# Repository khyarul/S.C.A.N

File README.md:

# S.C.A.N
 Small and Cheap Attendance Node

## Attendance Node Machine
   - Hardware: ESP8266 Wemos D1 Mini - Software: Arduino C/C++

   - Feature and library used:
     - [x] Dual Mode: **Tap to Unlock Door** and **Attendance Mode**
     - [x] Scheduler.h (Multitask) from [Here](https://github.com/nrwiersma/ESP8266Scheduler)
     - [x] PubSubClient.h (MQTT protocol client)
     - [x] LiquidCrystal_I2C.h (LCD16x2 I2C)
     - [x] MFRC522.h (RFID SPI module 13.56MHz)
     - [x] ArduinoOTA.h (wireless/no-usb programming)
     - [x] Reed/magnetic sensor for Door state
     - [x] solenoid door lock port max. 12V/1A (12W)
     - [x] 5V/3A (15W) power supply input
   
   - Recommended ESP8266 Wemos D1 Mini Arduino Configuration:

   - Wemos D1 Mini Port Allocation:
   
 PORT |	FUNCTION |	DEVICE
 -----|----------|-------   
 D1 |	I2C SCL |	LCD 16x2
 D2 |	I2C SDA |	LCD 16x2
 D4 |	SPI Reset |	RC522
 D5 |	SPI SCK |	RC522
 D6 |	SPI MISO |	RC522
 D7 |	SPI MOSI	| RC522
 D8 |	SPI SS	| RC522
 D0 |	Digital Output	| Solenoid
 TX |	Digital Input	| Attendance Mode button
 RX |	Digital Output |	Buzzer
 D3 |	Digital Input |	“Unlock Door” Mode button
 A0 |	Analog Input |	Magnetic Switch/Sensor

   - Mechanic Documentation Photo:
     - **Acrylic Case for LCD, RFID sensor, button, and buzzer. Install it outside the room.**

     - **Acrylic case for controller part, reed/magnet sensor and solenoid port. Install it inside the room.**

     - **Solenoid port and small hole for reed/magnet sensor wire**

## GUI (Node Monitor & Employee Manager)
- Tested on Windows 10 PC and Ubuntu Mate 18.04 64bit on Raspberry Pi 3 (Should be supported with Ubuntu 64bit on PC)
- Main file: **"SCAN_node_monitor.py"** (**"karyawan.py"**, **"icons"**, and **"images" need to be in the same folder**)

- Feature:
  - [x] Manage & monitor all Node Machine that connected to the same MQTT server.
  - [x] Using MongoDB database for Node & Employee Manager.
  - [x] Unlock door on every Node Machine remotely.

- Python 3.7 module/library used:
  - [x] Pyqt5 (for GUI)
  - [x] PyMongo (for MongoDB Database driver)
  - [x] Paho-Mqtt (MQTT client)
  - [x] Threading (Multitasking using Multithreading, 1 thread per 1 Attendance Node Machine)

## Support & DONATE this open source project:
  - PAYPAL  : [SentinelCreative](https://www.paypal.me/sentinelcreative "PAYPAL")
  - BNI     : 1284959883 (Khyarul Arham)
  - Jago    : 504120557241 (Khyarul Arham)

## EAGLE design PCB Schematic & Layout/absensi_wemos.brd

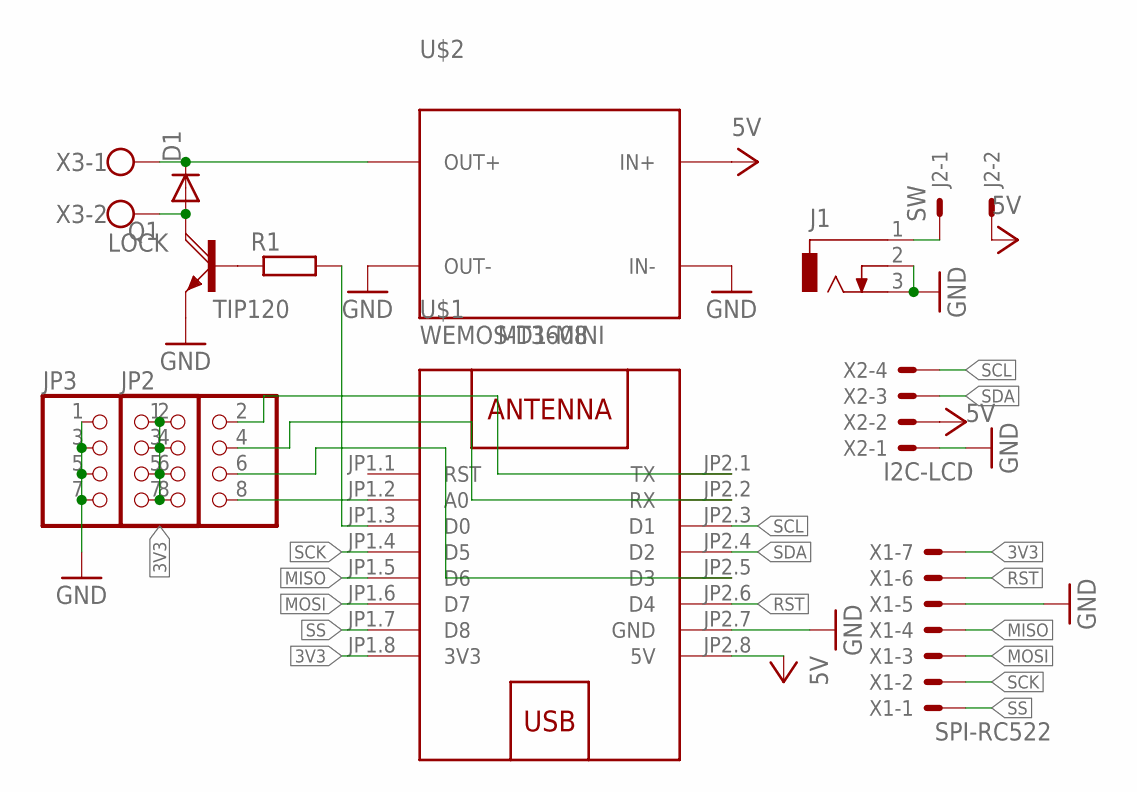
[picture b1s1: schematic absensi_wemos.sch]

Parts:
D1: DIODE-DO-214AC; DO-214AC
J1: DCJ0303
J2: SW; 6410-02
JP2, JP3: PINHD-2X4; 2X04
Q1: TIP120; TO220AH
R1: R0207/10; 0207/10
U$1: WEMOS-D1-MINI
U$2: MT3608; DC-DC-STEP-UP-MT3608
X1: SPI-RC522; 6410-07
X2: I2C-LCD; 6410-04
X3: LOCK; W237-102

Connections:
3V3: JP2.1, JP2.3, JP2.5, JP2.7, JP3.2, JP3.4, JP3.6, JP3.8, U$1.JP1.8 (3V3), X1.7
GND: J1.2, J1.3, JP3.1, JP3.3, JP3.5, JP3.7, Q1.E, U$1.JP2.7 (GND), U$2.IN-, U$2.OUT-, X1.5, X2.1
MISO: U$1.JP1.5 (D6), X1.4
MOSI: U$1.JP1.6 (D7), X1.3
unnamed: J1.1, J2.1
unnamed: R1.2, U$1.JP1.3 (D0)
unnamed: Q1.B, R1.1
unnamed: D1.C, U$2.OUT+, X3.1
unnamed: D1.A, Q1.C, X3.2
unnamed: JP2.8, U$1.JP1.2 (A0)
unnamed: JP2.6, U$1.JP2.5 (D3)
unnamed: JP2.4, U$1.JP2.2 (RX)
unnamed: JP2.2, U$1.JP2.1 (TX)
RST: U$1.JP2.6 (D4), X1.6
SCK: U$1.JP1.4 (D5), X1.2
SCL: U$1.JP2.3 (D1), X2.4
SDA: U$1.JP2.4 (D2), X2.3
SS: U$1.JP1.7 (D8), X1.1
VCC: J2.2, U$1.JP2.8 (5V), U$2.IN+, X2.2

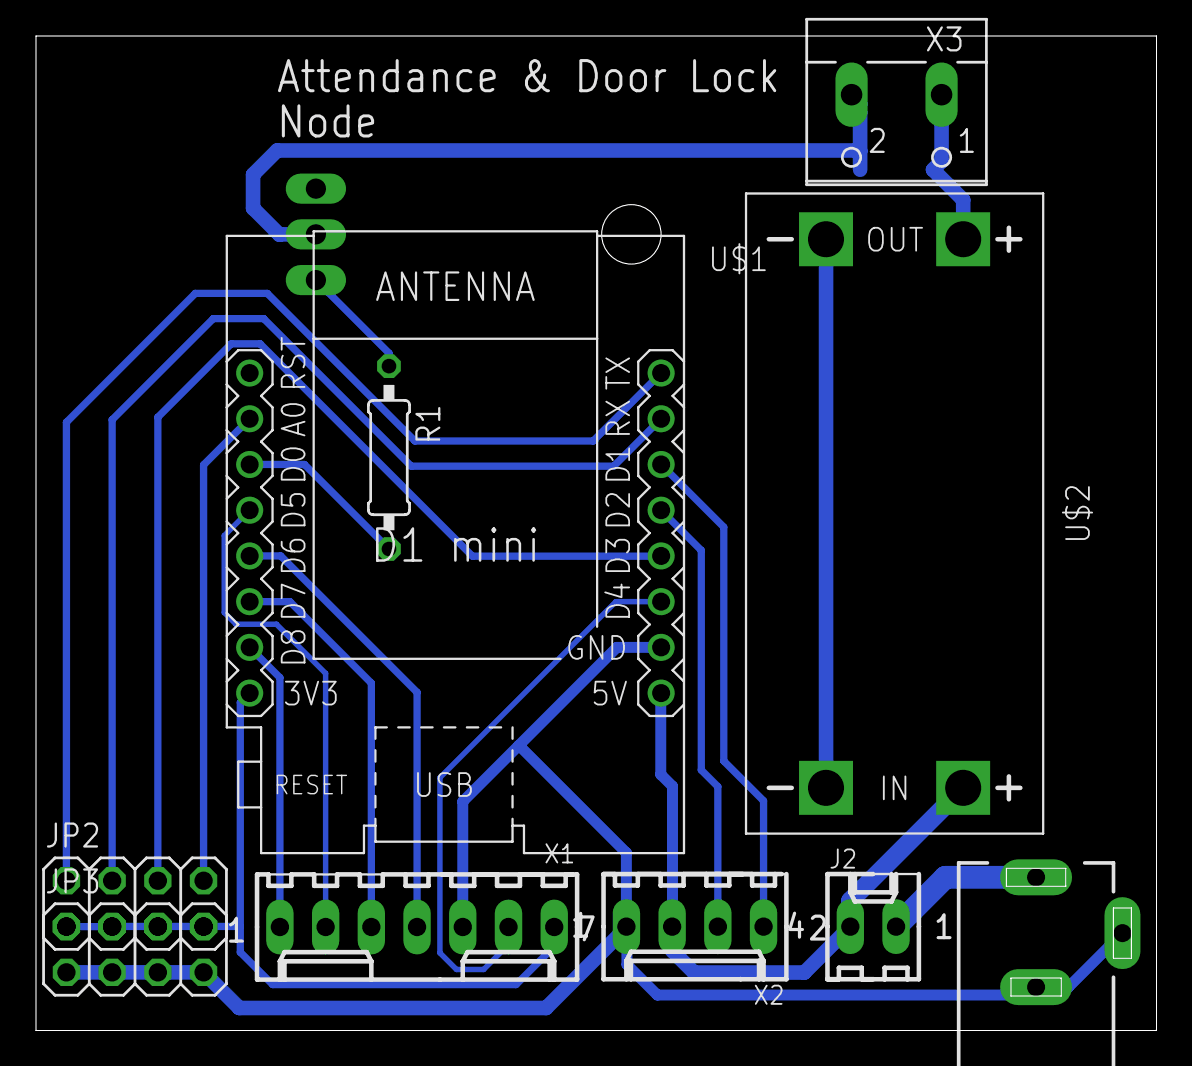
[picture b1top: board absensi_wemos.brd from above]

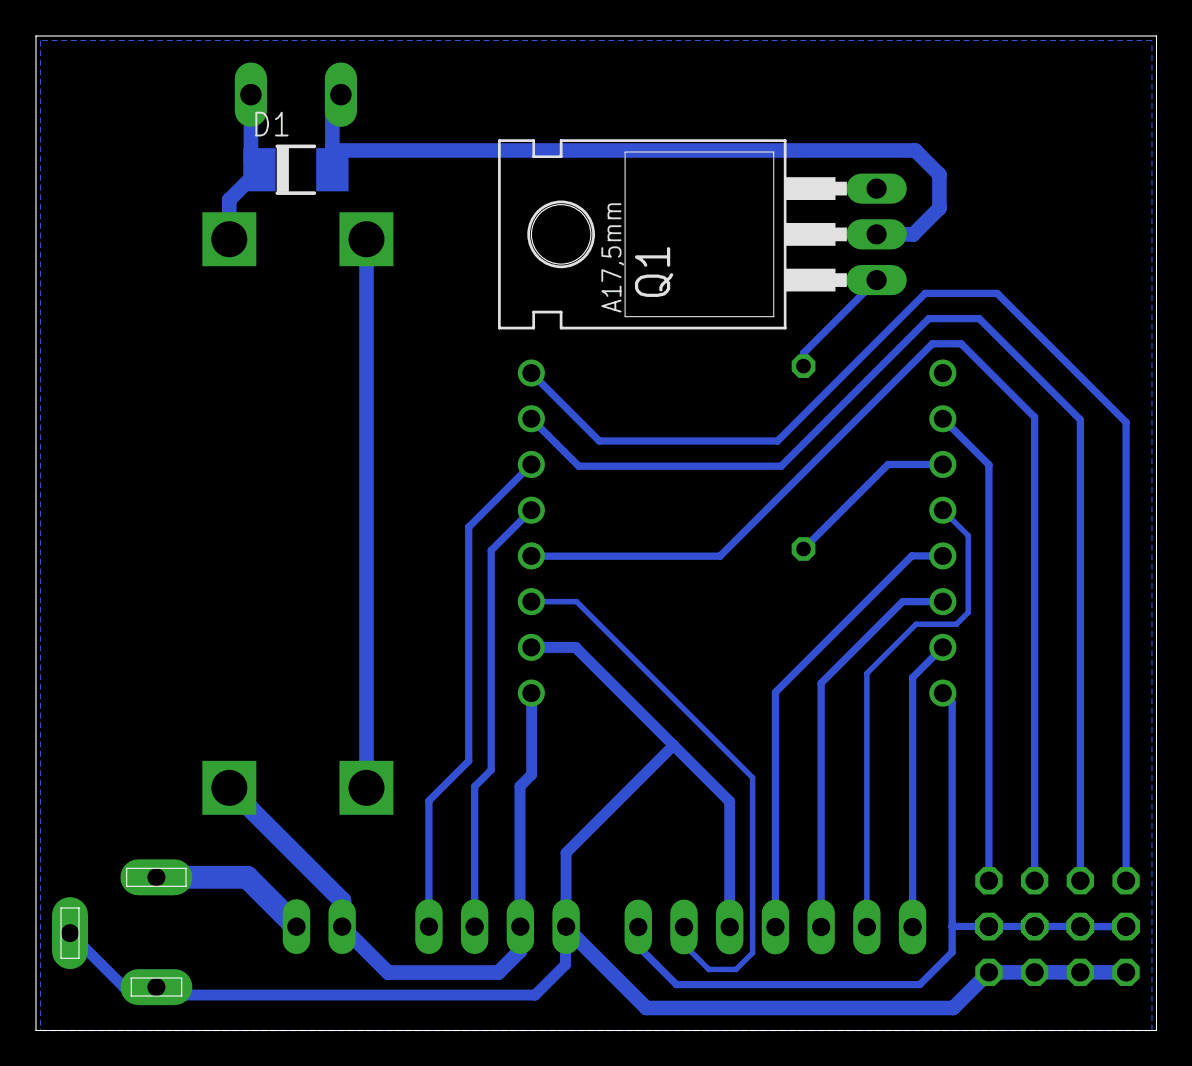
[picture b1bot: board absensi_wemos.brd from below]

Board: 2 copper layers, 62.2 x 55.2 mm, 12 parts (2 on the bottom side), 19 nets.

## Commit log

2020-05-09 GUI file
    Python GUI file
2020-05-11 PCB & Case
    PCB: eagle file
    Case: corel draw
2020-05-11 Arduino code
2020-05-11 Python GUI PyQt5
2020-05-13 Proposal Skripsi
    Proposal Skripsi
2020-05-17 PyQt5 Desktop GUI
    PyQt5 Desktop GUI
2020-05-17 Update SCAN_node_monitor.py
    client.subscribe('UID/' + clientID)
2020-05-17 New dual mode feature
2020-05-17 Update SCAN_node_monitor.py
    fix some bugs on Dual Mode
2020-05-18 Dual Mode & Door Status
2020-05-18 Version 1.0
    release v1.0: Node Monitor & Employee Manager (GUI) and Node firmware (Arduino: Wemos D1 Mini)
2020-05-18 Version 1.0 update
    add enableConfig() methode
2020-05-22 Multi OS Bug fix
    Multi OS Bug fix (Windows and Linux Ubuntu), calling "karyawan.py" must using specific command "python3" on Linux
2020-05-22 Update S.C.A.N_OTA.ino
    delete my personal config
2020-05-30 Proposal Skripsi
2020-06-03 -Added "responTime" and "now" var for measuring the amount of time needed for authentication process -responTime published on "PERIOD" topic, will be added to Log Event on Node Monitor -added timeout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
2020-06-03 Update SCAN_node_monitor.py
    -subscribe to 'PERIOD' topic to measure amount time needed on authentication process (Node client store it on 'PERIOD' topic)
    -Also display the result to Log Event
2020-06-03 -bug fix on authentication process (timeout and response)
2020-07-14 config MQTT authentication using "auth"
2020-07-14 Fix stability & memory issue
    -use '' instead of str() to increase stability
    -add configurable variable, fix overflow memory issue
2020-07-21 Update S.C.A.N_OTA.ino
    -MQTT server parameter is configurable on line 26 to 31
    -OTA server parameter is configurable on line 33 to 34
    -tested by me until 12 hours long (hope it's working for 24/7 nonstop) - ALWAYS MEMORY PROBLEM... ALWAYS...
2020-07-22 Update SCAN_node_monitor.py
    don't convert directly "int" to "string" inside "publish" method, it's causing stability issue
2020-07-24 Update SCAN_node_monitor.py
    Bug fix on "DOOR STATUS" and "CONNECTION STATUS" state change
2020-07-24 Create SKRIPSI.docx
    sedang rajin-rajinnya
2020-08-20 Jurnal, Poster, SOP (manual)

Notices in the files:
parts and their libraries:
diy-modules: Released under the Creative Commons Attribution 4.0 International License: http://creativecommons.org/licenses/by/4.0
